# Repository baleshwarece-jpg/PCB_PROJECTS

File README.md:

# 30-Day PCB Design Challenge

A self-directed challenge to design, document, and release one original PCB per day for 30 consecutive days using KiCad 8. Each board lives in its own folder with complete hardware source files, gerbers, a bill of materials, and a standalone README covering the design rationale, schematic walkthrough, layout decisions, and common troubleshooting for that specific circuit.

The boards span power conversion, motor and LED driving, sensor interfacing, audio, wireless communication, and digital logic — chosen to force repeated practice across the categories of circuits that come up most often in embedded and electronics projects, rather than 30 variations on a single theme.

## Goals

- Build daily fluency with KiCad 8: schematic capture, footprint selection, layout, and gerber generation, fast enough to take a board from concept to fabrication-ready in a single day
- Practice real engineering judgment on every board — component selection backed by datasheet parameters, trace widths backed by IPC-2221, decoupling and grounding decisions backed by the actual current and noise behavior of the circuit, not copied defaults
- Produce documentation good enough that another engineer could understand, build, and troubleshoot each board without needing to ask questions
- Cover a broad enough range of circuit types that the challenge functions as a personal reference library going forward

## Repository Structure

Each day's board lives in its own top-level folder:

```
<repo-root>/
├── Day-01-AC-DC-Regulator/
├── Day-02-Transformerless-Power-Supply/
├── Day3_ServoTester/
├── Day4_MotorSpeedController/
├── DAY-5-LM389/
├── Day6-usb-5v-power-supply/
├── Day7-3.3v-LDO/
├── DAY8-ARDUINO-EXTENSIONBOARD/
├── Day9_pushbutton-led-controller/
├── Day10-DHT11/
├── Day11-I2C-OLED-ADAPTER/
├── Day12-IR-remote-receiver/
├── Day13_PIEZO-BUZZER/
├── DAY-14_LDRMODULE/
├── DAY15-RELAYMODULE/
├── DAY16-4LEV_BATTERY_INDICATOR/
├── DAY17-MCP23017-I2C-GPIO-Expander-Board/
├── DAY18_USB-UART-CONVERTER/
├── DAY19-WS2812B_RGB_LED_CONTROL/
├── DAY20-MOSFET_H_BRIDGE-MOTOR-DRIVER/
├── DAY21-Low-Power-Microphone-Preamplifier/
├── Day22-MCP2551-CAN-Bus-Transceiver-Breakout/
├── DAY23-SOIL_MOISTURE_SENSOR/
├── DAY24-NRF24-MODULE/
├── DAY25-LM2596-Adjustable-Buck-Converter/
├── DAY26-MAX7219-8-Digit-LED-Display-Driver/
├── DAY27-TPS61023-3.7V-LiPo-to-5V/
├── DAY28-74HC138-3-to-8/
├── DAY29-MPU6050/
└── DAY30-PAM8403-Class-D-Stereo-Amplifier/
```

Every folder follows the same internal layout:

```
DayNN-BoardName/
├── hardware/
│   ├── *.kicad_pro / *.kicad_sch / *.kicad_pcb
│   ├── gerbers/
│   └── bom/
├── docs/
│   ├── schematic.pdf
│   ├── datasheet(s)
│   └── assembly_notes.md
└── README.md
```

## Board Index

| Day | Board | Category |
|---|---|---|
| 01 | AC-DC Regulator | Power |
| 02 | Transformerless Power Supply | Power |
| 03 | Servo Tester | Motor / Actuator |
| 04 | Motor Speed Controller | Motor / Actuator |
| 05 | LM389 Audio Amplifier | Audio |
| 06 | USB to 5V Power Supply | Power |
| 07 | 3.3V LDO Regulator | Power |
| 08 | Arduino Extension Board | Prototyping |
| 09 | Pushbutton LED Controller | Digital I/O |
| 10 | DHT11 Temperature/Humidity Sensor Breakout | Sensor |
| 11 | I2C OLED Adapter | Display |
| 12 | IR Remote Receiver | Sensor / Comms |
| 13 | Piezo Buzzer Driver | Audio / Digital I/O |
| 14 | LDR Module | Sensor |
| 15 | Relay Module | Power / Switching |
| 16 | 4-Level Battery Indicator | Power / Sensor |
| 17 | MCP23017 I2C GPIO Expander | Digital Logic |
| 18 | USB to UART Converter | Comms |
| 19 | WS2812B RGB LED Strip Driver | LED / Motor-Adjacent |
| 20 | MOSFET H-Bridge Motor Driver | Motor / Actuator |
| 21 | Low-Power Microphone Preamplifier | Audio |
| 22 | MCP2551 CAN Bus Transceiver Breakout | Comms |
| 23 | Resistive Soil Moisture Sensor | Sensor |
| 24 | nRF24L01+ Wireless Module Adapter | Wireless |
| 25 | LM2596 Adjustable Buck Converter | Power |
| 26 | MAX7219 8-Digit LED Display Driver | Display |
| 27 | TPS61023 3.7V LiPo to 5V Boost Converter | Power |
| 28 | 74HC138 3-to-8 Line Decoder Breakout | Digital Logic |
| 29 | MPU6050 IMU Breakout | Sensor |
| 30 | PAM8403 Class-D Stereo Amplifier | Audio |

## Tooling

- **EDA:** KiCad 8
- **Fabrication target:** JLCPCB / PCBWay standard capabilities (2-layer, 1 oz / 2 oz copper depending on board, 0.6 mm minimum trace/space unless otherwise noted in a given board's README)
- **Reference standards:** IPC-2221 for trace current capacity; manufacturer datasheets for every active component's electrical and thermal limits

## Documentation Conventions

Every board's README follows a consistent structure: an overview of what the circuit does and why it's built the way it is, a full specifications table, a "why this design" section explaining the engineering reasoning behind component and layout choices (not just what the choices were), a per-component schematic walkthrough, PCB layout notes, getting-started wiring and code examples where applicable, a complete BOM with real part numbers, and a troubleshooting section covering realistic failure modes rather than generic advice.

## License

All hardware design files across this repository are released under **CERN OHL v2 — Permissive**, unless a specific board's folder states otherwise.

## Status

Challenge complete — 30 boards designed across 30 days, all folders accounted for. Individual board READMEs contain full design detail; this top-level README serves as the index.

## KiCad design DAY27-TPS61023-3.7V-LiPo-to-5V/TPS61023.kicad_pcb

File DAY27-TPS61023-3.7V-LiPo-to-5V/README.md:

# TPS61023 3.7V LiPo to 5V Boost Converter

**Day 27 / 30 — 30-Day PCB Design Challenge**

A single-cell LiPo to 5V step-up (boost) converter built around the TPS61023, a synchronous boost regulator with integrated power FETs, true load disconnect, and a 2.4 A switch current limit — purpose-built for portable projects that need a stable 5V rail from a single-cell lithium battery as it discharges from 4.2V down to 3.0V.

## Overview

A single-cell LiPo battery's terminal voltage spans roughly 3.0V (discharged cutoff) to 4.2V (full charge), straddling the 5V rail most peripherals and microcontroller boards expect. A linear regulator cannot produce 5V from a 3.7V-nominal source at all, since a linear regulator can only step voltage down. A boost converter is required, and the TPS61023 is a synchronous design — meaning the low-side switch is an actively driven FET rather than a passive diode, which removes the diode forward-voltage loss present in older asynchronous boost ICs and improves efficiency, particularly at low input voltages near end-of-discharge.

The TPS61023 also includes true shutdown (load disconnected from input during shutdown, unlike many boost ICs where the body diode of the synchronous FET still passes current to the load even when disabled) and a power-good output, both of which matter for battery-powered designs where parasitic leakage paths directly reduce runtime.

## Specifications

| Parameter | Value |
|---|---|
| Input Voltage | 0.5V – 5.5V (start-up requires ≥1.8V typical) |
| Output Voltage | 5.0V fixed (this board) — adjustable variants exist |
| Max Switch Current | 2.4A (internal current limit) |
| Max Output Current | ~1.2A at VIN = 3.0V, higher at higher VIN (load-line dependent) |
| Switching Frequency | 2.5 MHz typical |
| Quiescent Current | ~38 µA (device in regulation, no load) |
| True Shutdown | Yes — output disconnected from input via EN pin |
| Power Good Output | Open-drain, active high when VOUT within regulation |
| Package | SOT-23-Thin or WSON, this board uses SOT-23-Thin (6-pin) |
| PCB | 2-layer, 1 oz copper |

## Why a Dedicated Boost Board

A bare TPS61023 wired ad hoc on a breadboard will technically boost voltage, but several details determine whether it delivers rated current cleanly and survives a battery-powered duty cycle:

**Input capacitor placement and value:** At 2.5 MHz switching frequency, the inductor current ripple reflected onto the input rail needs low-ESR, low-ESL capacitance placed immediately at the VIN pin — a capacitor even 1 cm away on a long breadboard wire reintroduces enough parasitic inductance to produce audible noise (coil whine) and degraded efficiency. This board places the input ceramic capacitor directly adjacent to the VIN pin with minimal trace length.

**Output capacitor ESR and the feedback loop:** Boost converters are inherently right-half-plane-zero systems, meaning loop stability is more sensitive to output capacitor ESR than in a comparable buck design. The TPS61023's internal compensation is designed around the datasheet's recommended output capacitor range — substituting a much larger or much smaller value, or a high-ESR electrolytic, can degrade transient response or introduce ringing on load steps.

**Inductor saturation margin:** The boost topology's inductor carries higher peak current than the output current would suggest, since input current exceeds output current by roughly the inverse of efficiency times the voltage step-up ratio. At VIN = 3.0V boosting to 5V and drawing 1A out, input-side (and inductor) current approaches 1.85A even at 90% efficiency. An inductor saturation-rated only slightly above the IC's switch current limit will saturate under real load before the IC's own current limit engages, producing unpredictable output collapse rather than a clean current-limited response.

**True shutdown current path:** EN tied low disconnects the load from the battery entirely on this device, which only matters if the EN pin is actually routed to an accessible control point — many ad hoc breadboard builds simply tie EN high permanently, losing the ability to fully disconnect the battery for storage or fault conditions.

## Schematic Overview

**U1 — TPS61023**
Synchronous boost converter. VIN connects to the LiPo input. SW connects to the inductor switch node. VOUT is the regulated 5V output. EN is broken out to a control header with a pull-up to VIN for default-on behavior. PG (power good) is broken out as an open-drain output with an external pull-up.

**L1 — 1.5 µH Power Inductor**
Selected per the TPS61023 datasheet's recommended inductance range for 2.5 MHz switching. Saturation current rated at 4A — comfortably above the IC's 2.4A switch current limit to ensure the IC's current limit, not inductor saturation, defines the converter's overcurrent behavior.

**C1 — 10 µF Ceramic, X7R (Input)**
Input decoupling, placed directly at the VIN pin. X7R dielectric specified rather than X5R or lower grades to limit capacitance derating under DC bias and temperature, since ceramic capacitors lose significant effective capacitance as DC bias approaches their rated voltage.

**C2 — 22 µF Ceramic, X7R (Output)**
Output filter capacitor, within the TPS61023 datasheet's recommended range for stable loop compensation. Two parallel 22 µF capacitors are used on the footprint pads to split ripple current and reduce effective ESR further, though a single capacitor is sufficient for most loads.

**R1 — 100 kΩ Pull-up (EN)**
Pulls EN to VIN by default so the converter starts automatically when the battery is connected. EN header pin allows pulling this low externally (through a switch or MCU GPIO) to fully disconnect the load.

**R2 — 100 kΩ Pull-up (PG)**
Pull-up for the open-drain power-good output, referenced to VOUT so the PG signal swings to a valid logic high recognizable by a downstream 5V-logic MCU.

**J1 — Battery input**
2-pin JST-PH 2.0mm connector, standard polarity for common LiPo battery connectors.

**J2 — Output / control header**
4-pin, 2.54 mm: VOUT, GND, EN, PG.

**LED1 — Power-good indicator**
Green, 0603, driven from the PG pull-up node rather than directly from VOUT, so the LED only illuminates once the converter has actually reached regulation rather than simply being powered.

## PCB Design Notes

- Designed in KiCad 8
- 1 oz copper, 2-layer — sufficient for the ~1–2A current levels involved given short, wide power traces
- Switch node (U1 SW → L1) kept short and on a single layer to minimize parasitic inductance and EMI radiation at 2.5 MHz
- Input capacitor (C1) placed on the same side as U1 with trace length to VIN under 3 mm
- Output capacitor (C2) placed adjacent to VOUT, ground return tied directly into the ground pour beneath the IC
- Ground pour on both layers, stitched with vias around the IC and inductor footprint
- Feedback/PG/EN traces routed away from the switch node to avoid noise injection into control signals
- Battery connector polarity clearly marked on silkscreen, reverse-polarity protection diode footprint provided as an optional series component on VIN (not populated by default, since the TPS61023 itself has no reverse-input protection)
- Mounting holes: 2× M2.5, diagonal corners

## Getting Started

### Wiring

```
LiPo Battery (3.7V nominal)     Boost Board           Load (5V)
─────────────────────────────────────────────────────────────────
JST-PH connector  ──────>       J1 (VIN/GND)
                                  VOUT       ──────>    + Load
                                  GND        ──────>    − Load
                                  EN         ──────>    (tied high by default)
                                  PG         ──────>    optional MCU input
```

A LiPo protection circuit (over-discharge, over-current) is assumed to be present either in the battery pack itself or upstream of this board — the TPS61023 provides no battery protection functions on its own.

### Checking Power-Good Status (Arduino example)

```cpp
const int PG_PIN = 2;

void setup() {
  pinMode(PG_PIN, INPUT);
  Serial.begin(9600);
}

void loop() {
  bool regulating = digitalRead(PG_PIN);
  Serial.println(regulating ? "5V rail OK" : "5V rail not in regulation");
  delay(500);
}
```

## BOM

| Reference | Part | Package | Value / Part No. |
|---|---|---|---|
| U1 | TPS61023 | SOT-23-Thin (6-pin) | Synchronous boost converter |
| L1 | Shielded power inductor | 3×3 mm | 1.5 µH, Isat > 4A |
| C1 | Ceramic, X7R | 0805 | 10 µF / 10V |
| C2 | Ceramic, X7R | 0805 | 22 µF / 10V |
| R1 | Resistor | 0402 | 100 kΩ (EN pull-up) |
| R2 | Resistor | 0402 | 100 kΩ (PG pull-up) |
| R3 | Resistor | 0402 | 1 kΩ (LED current limit) |
| LED1 | Green LED | 0603 | Power-good indicator |
| J1 | JST-PH connector | 2.0 mm, 2-pin | Battery input |
| J2 | Pin header | 2.54 mm, 4-pin | Output / control |

## Common Issues

**Output sags or shuts down under load near end-of-discharge**
Expected behavior as the battery approaches its discharge cutoff — the IC needs sufficient input voltage headroom to maintain the duty cycle required for 5V output, and as VIN drops the maximum deliverable output current also drops. Check the actual battery voltage under load with a meter before assuming a board fault.

**Audible whine from the inductor**
Usually indicates either light-load operation triggering pulse-skipping mode (some buzz is normal and not damaging) or insufficient input capacitance allowing ripple current through the inductor at audible sub-harmonics. Confirm C1 is populated and properly soldered before assuming the inductor itself is at fault.

**PG pin never goes high**
Confirm R2 is populated — PG is open-drain and will float or read indeterminate without an external pull-up. Also verify VOUT is actually reaching 5V; PG asserts only once the output is within the IC's regulation window.

**No output despite input voltage present**
Check EN is pulled high — if R1 is missing or EN is inadvertently grounded through the control header, the converter remains in shutdown regardless of VIN.

**Converter does not start from a fully discharged battery**
The TPS61023 requires a minimum input voltage (datasheet typical ~1.8V) to begin switching. A battery below its rated discharge cutoff (commonly 3.0V) should not be relied upon to start the converter — this is a battery protection concern as much as a converter one.

## Repository Structure

```
TPS61023-Boost-Converter/
├── hardware/
│   ├── TPS61023_Boost.kicad_pro
│   ├── TPS61023_Boost.kicad_sch
│   ├── TPS61023_Boost.kicad_pcb
│   ├── gerbers/
│   │   └── TPS61023_Boost_gerbers.zip
│   └── bom/
│       └── TPS61023_Boost_BOM.csv
├── docs/
│   ├── schematic.pdf
│   ├── TPS61023_Datasheet.pdf
│   └── assembly_notes.md
└── README.md
```

## 30-Day PCB Challenge Progress

| Day | Board | Status |
|---|---|---|
| 25 | LM2596 Adjustable Buck Converter | Complete |
| 26 | MAX7219 8-Digit LED Display Driver | Complete |
| 27 | TPS61023 3.7V LiPo to 5V Boost Converter | Complete |
| 28 | Coming soon | — |

## License

Hardware design files released under CERN OHL v2 — Permissive.

## References

- TPS61023 Datasheet — Texas Instruments
- KiCad EDA

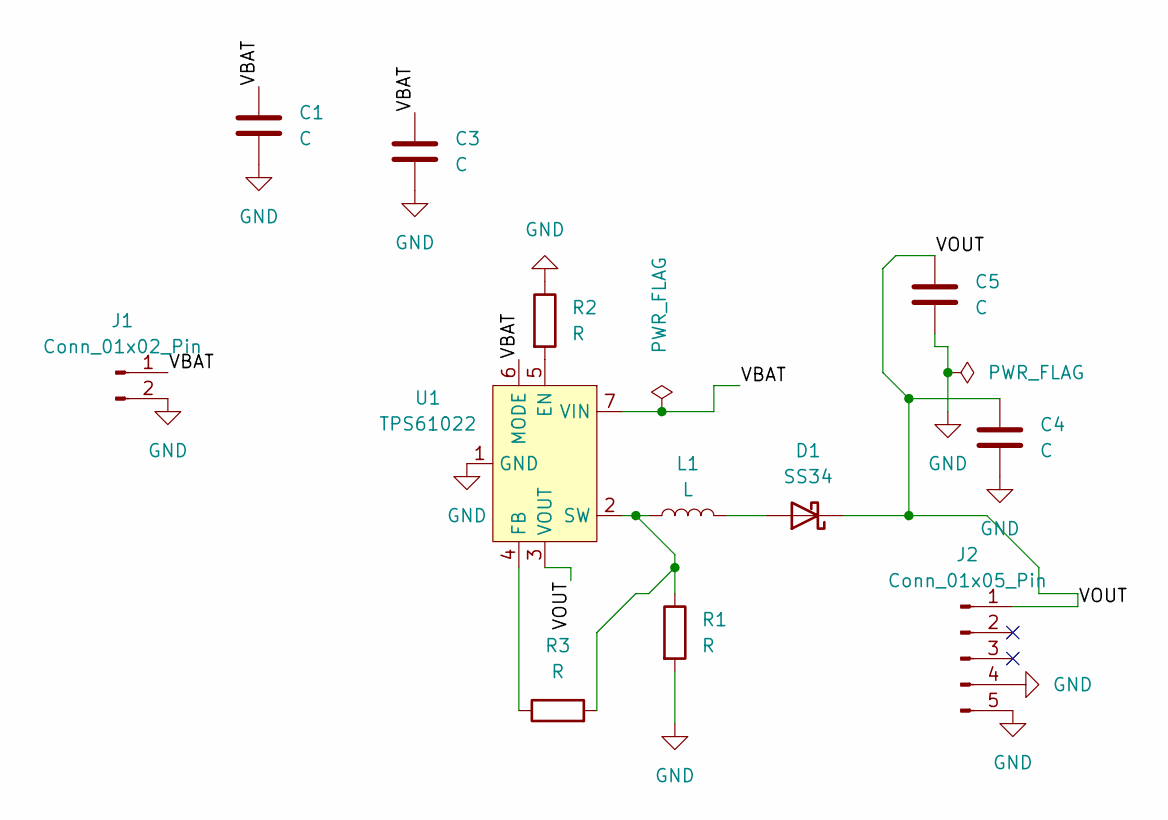
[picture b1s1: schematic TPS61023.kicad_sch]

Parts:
C1, C3, C4, C5: C; C_0603_1608Metric_Pad1.08x0.95mm_HandSolder
D1: SS34; D_SMA
J1: Conn_01x02_Pin; PinHeader_1x02_P2.54mm_Vertical
J2: Conn_01x05_Pin; PinHeader_1x05_P2.54mm_Horizontal
L1: L; L_0603_1608Metric_Pad1.05x0.95mm_HandSolder
R1, R2, R3: R; R_0603_1608Metric_Pad0.98x0.95mm_HandSolder
U1: TPS61022; Texas_RWU0007A_VQFN-7_2x2mm_P0.5mm

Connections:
/VBAT: C1.1, C3.1, J1.1, U1.6 (MODE), U1.7 (VIN); also elsewhere on the board
/VOUT: C4.1, C5.1, D1.1 (K), J2.1, U1.3 (VOUT)
GND: C1.2, C3.2, C4.2, C5.2, J1.2, J2.4, J2.5, R1.2, R2.1, U1.1 (GND); also elsewhere on the board
unnamed: D1.2 (A), L1.2
unnamed: R2.2, U1.5 (EN)
unnamed: R3.1, U1.4 (FB)
unnamed: L1.1, R1.1, R3.2, U1.2 (SW)

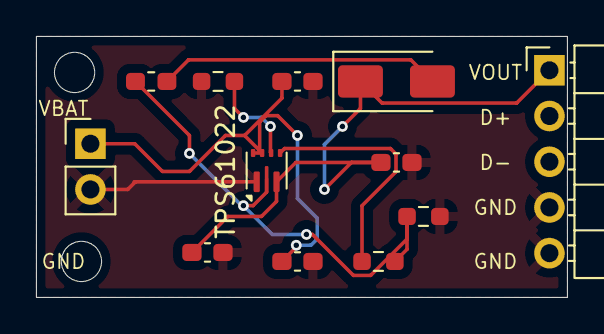
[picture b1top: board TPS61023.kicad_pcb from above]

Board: 2 copper layers, 29.5 x 14.5 mm, 12 parts (0 on the bottom side), 7 nets.

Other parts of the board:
VBAT: Conn_01x02_Pin; PinHeader_1x02_P2.54mm_Vertical

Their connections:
/VBAT: VBAT.1; also elsewhere on the board
GND: VBAT.2; also elsewhere on the board

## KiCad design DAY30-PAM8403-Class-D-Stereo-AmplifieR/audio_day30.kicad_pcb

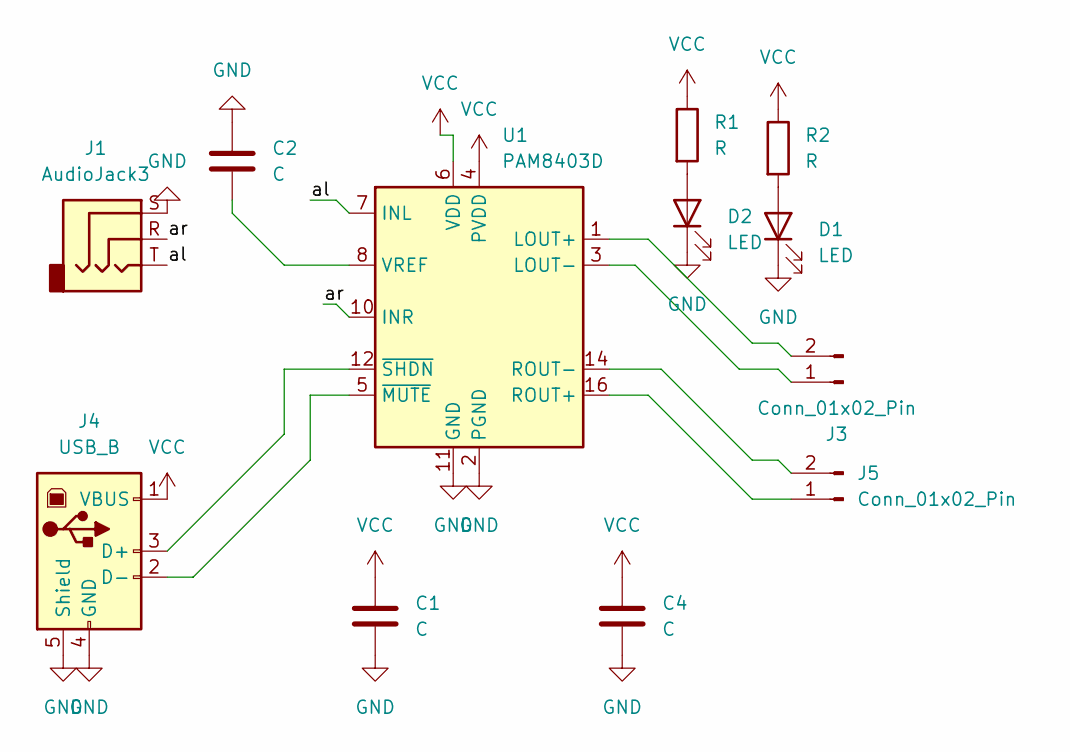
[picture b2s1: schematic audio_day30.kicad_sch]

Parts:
C1, C2, C4: C; C_0603_1608Metric_Pad1.08x0.95mm_HandSolder
D1, D2: LED; LED_0603_1608Metric_Pad1.05x0.95mm_HandSolder
J1: AudioJack3; Jack_3.5mm_CUI_SJ1-3523N_Horizontal
J3, J5: Conn_01x02_Pin; PinHeader_1x02_P2.54mm_Vertical
J4: USB_B; USB_Mini-B_Lumberg_2486_01_Horizontal
R1, R2: R; R_0805_2012Metric_Pad1.20x1.40mm_HandSolder
U1: PAM8403D; SOIC-16_3.9x9.9mm_P1.27mm

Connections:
/al: J1.T, U1.7 (INL)
/ar: J1.R, U1.10 (INR)
GND: C1.2, C2.1, C4.2, D1.1 (K), D2.1 (K), J1.S, J4.4 (GND), J4.5 (Shield), U1.2 (PGND), U1.11 (GND), U1.15 (PGND)
unnamed: D1.2 (A), R2.2
unnamed: D2.2 (A), R1.2
unnamed: J3.1, U1.3 (LOUT-)
unnamed: J3.2, U1.1 (LOUT+)
unnamed: J4.3 (D+), U1.12 (~SHDN)
unnamed: J4.2 (D-), U1.5 (~MUTE)
unnamed: J5.1, U1.16 (ROUT+)
unnamed: J5.2, U1.14 (ROUT-)
unnamed: C2.2, U1.8 (VREF)
VCC: C1.1, C4.1, J4.1 (VBUS), R1.1, R2.1, U1.4 (PVDD), U1.6 (VDD), U1.13 (PVDD)

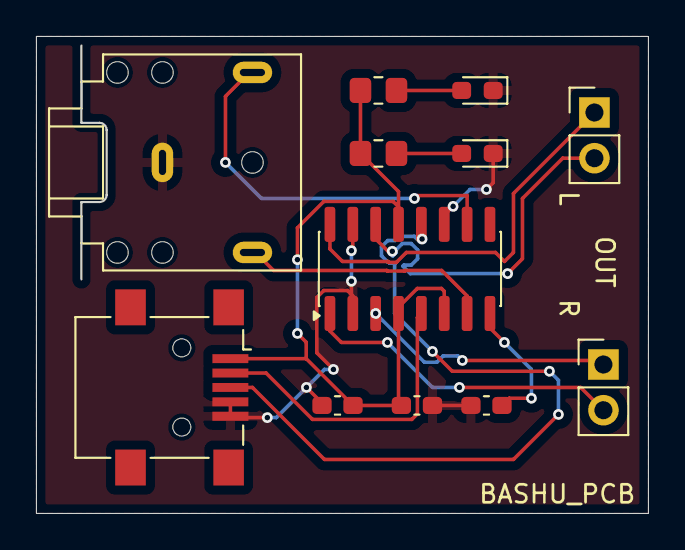
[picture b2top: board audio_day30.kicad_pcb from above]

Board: 2 copper layers, 34.0 x 26.5 mm, 12 parts (0 on the bottom side), 13 nets.

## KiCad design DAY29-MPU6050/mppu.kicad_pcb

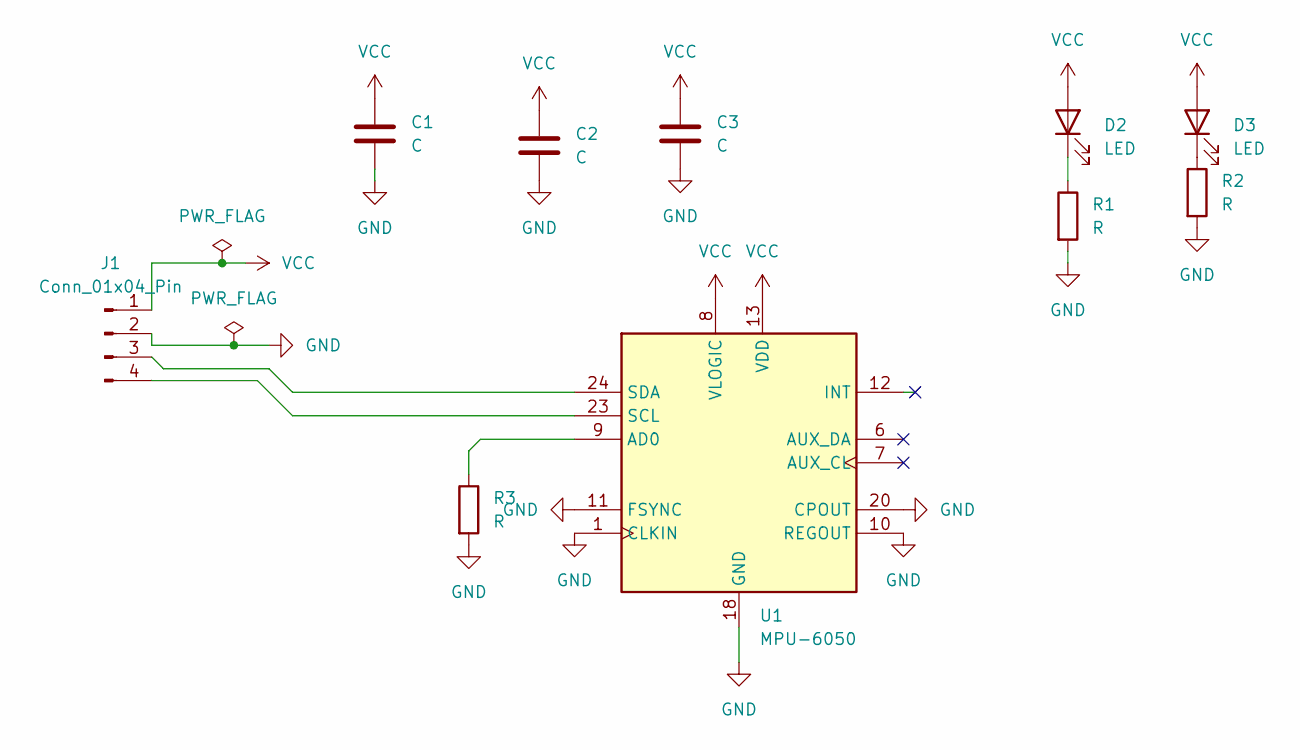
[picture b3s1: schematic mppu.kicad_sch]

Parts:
C1, C2, C3: C; C_0805_2012Metric_Pad1.18x1.45mm_HandSolder
D2, D3: LED; LED_0603_1608Metric_Pad1.05x0.95mm_HandSolder
J1: Conn_01x04_Pin; PinHeader_1x04_P2.54mm_Vertical
R1, R2, R3: R; R_0805_2012Metric_Pad1.20x1.40mm_HandSolder
U1: MPU-6050; InvenSense_QFN-24_4x4mm_P0.5mm

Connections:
GND: C1.2, C2.2, C3.2, J1.2, R1.2, R2.2, R3.2, U1.1 (CLKIN), U1.10 (REGOUT), U1.11 (FSYNC), U1.18 (GND), U1.20 (CPOUT)
unnamed: D2.1 (K), R1.1
unnamed: D3.1 (K), R2.1
unnamed: J1.3, U1.24 (SDA)
unnamed: J1.4, U1.23 (SCL)
unnamed: R3.1, U1.9 (AD0)
VCC: C1.1, C2.1, C3.1, D2.2 (A), D3.2 (A), J1.1, U1.8 (VLOGIC), U1.13 (VDD)

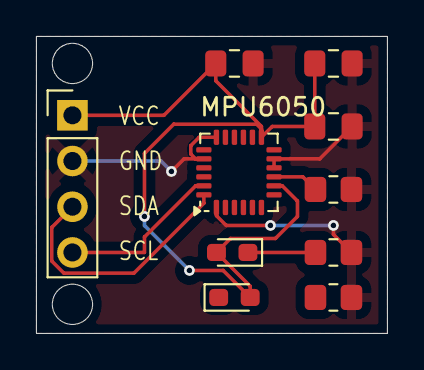
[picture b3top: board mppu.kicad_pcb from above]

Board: 2 copper layers, 19.5 x 16.5 mm, 10 parts (0 on the bottom side), 7 nets.

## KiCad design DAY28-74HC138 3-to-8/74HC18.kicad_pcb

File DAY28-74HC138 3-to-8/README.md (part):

# 74HC138 3-to-8 Line Decoder Breakout Board

**Day 28 / 30 — 30-Day PCB Design Challenge**

A breakout board for the 74HC138, a 3-to-8 line decoder/demultiplexer commonly used to extend a microcontroller's limited GPIO count into multiple chip-select lines for SPI peripherals, address decoding in memory-mapped designs, or driving up to 8 mutually-exclusive outputs from a 3-bit binary code.

## Overview

Many projects reach a point where a microcontroller runs out of dedicated chip-select or enable lines before it runs out of other I/O — a common case being multiple SPI devices on a shared bus, each needing its own CS line. Wiring 8 separate GPIOs as individual chip-selects works but consumes pins quickly and scales poorly. The 74HC138 takes a 3-bit binary address (A0–A2) plus three enable inputs and asserts exactly one of 8 active-low outputs at a time, meaning 3 GPIO pins can select among 8 devices instead of needing 8 dedicated lines.

This is a standard combinational logic part with no internal state or configuration registers — outputs change immediately and combinationally based on the address and enable inputs, with no clock or serial protocol involved. This board exists primarily to provide clean decoupling, a accessible header layout, and a documented reference for a part that gets reused across many other projects in this challenge series.

## Specifications

| Parameter | Value |
|---|---|
| Supply Voltage | 2V – 6V (4.5V–5.5V typical for this board) |
| Logic Family | 74HC (CMOS), 5V-tolerant inputs at VCC = 5V |
| Propagation Delay | ~18 ns typical (VCC = 5V, address to output) |
| Output Type | Active-low, push-pull (not open-drain) |
| Output Current | ±6 mA per output (HC family standard) |
| Address Inputs | A0, A1, A2 (3-bit binary select) |
| Enable Inputs | E1 (active-low), E2 (active-low), E3 (active-high) |
| Outputs | Y0–Y7, active-low, one asserted at a time |
| Package | SOIC-16 |
| PCB | 2-layer, 1 oz copper |

## Why a Breakout Board for a Simple Logic IC

The 74HC138 has no failure modes exotic enough to justify much circuit complexity, but a few practical details make a dedicated board worth having on hand rather than dead-bugging the IC into a project each time:

**Unused enable pins left floating:** The 74HC138 has three enable inputs (E1, E2 active-low; E3 active-high) — all three must be in their active state for any output to assert. A breadboard wiring mistake that leaves one enable pin floating produces unpredictable output behavior, since CMOS inputs left floating can settle at intermediate voltages and draw excess supply current or oscillate. This board ties E2 and E3 to their active states by default via solder-jumper pads, leaving only E1 broken out to a header pin for the common use case of a single active-low chip-enable signal from the host MCU.

**Decoupling for clean address transitions:** Like any CMOS logic device, the 74HC138 draws a brief current spike each time multiple outputs switch simultaneously during an address change (one output deasserting while another asserts). Without local decoupling this can show up as a glitch on the shared supply rail, which on a board with other sensitive analog or RF circuitry sharing the same rail is worth avoiding even though the HC138 itself is a low-power part.

**Output glitching during address transitions:** Because this is a combinational (not latched) decoder, outputs can briefly glitch through unintended states during an address transition if the three address bits do not change perfectly simultaneously — a phenomenon inherent to ripple-through binary decoding, not a fault of this board. Devices sensitive to brief false chip-select pulses (some SPI flash parts, for example) may need the enable pin gated by the host MCU only after address lines have settled, which is a software/timing consideration documented here rather than something correctable in hardware.

## Schematic Overview

**U1 — 74HC138**
3-to-8 decoder. A0–A2 address inputs from the header. E1 active-low enable from the header. E2 tied low via solder jumper (default enabled). E3 tied high via solder jumper (default enabled). Y0–Y7 outputs broken out to the output header.

**C1 — 100 nF Ceramic**
Local decoupling at VCC, placed within 2 mm of the IC supply pin per standard CMOS logic decoupling practice.

**JP1, JP2 — Solder jumpers (E2, E3 default state)**
Default-closed jumpers tying E2 low and E3 high so the device is enabled out of the box using only the E1 pin as an active-low chip enable. Can be cut and the pads broken out to header pins instead if all three enables need independent control for a specific application (e.g., using the decoder as a true 4-to-16 demultiplexer with a second 74HC138).

**J1 — Input header**
5-pin, 2.54 mm: VCC, GND, A0, A1, A2.

**J2 — Enable header**
2-pin, 2.54 mm: E1, GND (reference for an external pull-down switch or direct MCU GPIO connection).

**J3 — Output header**
8-pin, 2.54 mm: Y0–Y7, silkscreen-labeled in binary order matching the truth table for unambiguous wiring.

**LED1 — Power indicator**
Green, 0603, 1 kΩ series resistor from VCC, independent of the decoder outputs.

## Truth Table Reference

| E1 | E2 | E3 | A2 A1 A0 | Active Output |
|---|---|---|---|---|
| H | X | X | XXX | None (all outputs HIGH) |
| X | H | X | XXX | None (all outputs HIGH) |
| X | X | L | XXX | None (all outputs HIGH) |
| L | L | H | 000 | Y0 LOW |
| L | L | H | 001 | Y1 LOW |
| L | L | H | 010 | Y2 LOW |
| L | L | H | 011 | Y3 LOW |
| L | L | H | 100 | Y4 LOW |
| L | L | H | 101 | Y5 LOW |
| L | L | H | 110 | Y6 LOW |
| L | L | H | 111 | Y7 LOW |

## PCB Design Notes

- Designed in KiCad 8
- 1 oz copper, 2-layer — currents involved are well under 10 mA per line, so the layout priority is clean labeling and connector accessibility rather than current capacity
- C1 placed directly adjacent to VCC pin with the shortest practical ground return to the ground pour
- Address input traces (A0–A2) kept equal length where practical to minimize skew-induced output glitching during fast address transitions
- Output header silkscreen labeled Y0–Y7 directly above each pin, with the corresponding 3-bit binary address also silkscreened beneath each label for quick reference without consulting the datasheet
- Ground pour on both layers, stitched with vias around the IC footprint
- Mounting holes: 2× M2.5, diagonal corners

## Getting Started

### Wiring (single chip-enable use case)

```
Host MCU                   Decoder Board          Selected Devices
──────────────────────────────────────────────────────────────────
5V              ──────>    VCC
GND             ──────>    GND
GPIO (A0)       ──────>    A0
GPIO (A1)       ──────>    A1
GPIO (A2)       ──────>    A2
GPIO (E1, active-low) ──>  E1
                            Y0–Y7      ──────>    Individual CS pins
```

E2 and E3 remain tied to their active states via the default-closed solder jumpers; only E1 needs to be driven, low to enable decoding and high to force all outputs inactive.

### Arduino Example (selecting one of 8 SPI devices)

```cpp
const int A0_PIN = 2;
const int A1_PIN = 3;
const int A2_PIN = 4;
const int E1_PIN = 5;

void setup() {
  pinMode(A0_PIN, OUTPUT);
  pinMode(A1_PIN, OUTPUT);
  pinMode(A2_PIN, OUTPUT);
  pinMode(E1_PIN, OUTPUT);
  digitalWrite(E1_PIN, HIGH); // start disabled
}

void selectDevice(uint8_t index) {
  digitalWrite(E1_PIN, HIGH);          // disable while address settles
  digitalWrite(A0_PIN, index & 0x01);
  digitalWrite(A1_PIN, (index >> 1) & 0x01);
  digitalWrite(A2_PIN, (index >> 2) & 0x01);
  digitalWrite(E1_PIN, LOW);           // enable once address is stable
}

void loop() {
  selectDevice(3); // asserts Y3
  // ... perform SPI transaction with device 3 ...
  digitalWrite(E1_PIN, HIGH); // deselect before changing address again
  delay(100);
}
```

## BOM

| Reference | Part | Package | Value / Part No. |
|---|---|---|---|
| U1 | 74HC138 | SOIC-16 | 3-to-8 line decoder |
| C1 | Ceramic | 0603 | 100 nF / 16V |
| R1 | Resistor | 0402 | 1 kΩ (LED current limit) |
| LED1 | Green LED | 0603 | Power indicator |
| JP1, JP2 | Solder jumper pads | — | E2/E3 default-state straps |
| J1 | Pin header | 2.54 mm, 5-pin | VCC, GND, A0–A2 |
| J2 | Pin header | 2.54 mm, 2-pin | E1, GND |
| J3 | Pin header | 2.54 mm, 8-pin | Y0–Y7 outputs |

## Common Issues

**No output ever asserts, all outputs stay high**
Check that both solder jumpers JP1 (E2) and JP2 (E3) are intact and that E1 is actually being driven low — all three enable conditions must be satisfied simultaneously, not just E1.

**Wrong output asserts for a given address**
Verify A0 is the least significant bit, not A2 — this is a common wiring swap. Cross-reference against the truth table silkscreened beneath the output header.

**Brief glitches on unintended outputs during address changes**
Expected behavior of a combinational decoder if address bits do not transition simultaneously. If driving a device sensitive to brief false selection, gate the connected device's chip-select-sensitive operation through E1 as shown in the example code: disable via E1 before changing the address, then re-enable once the address lines have settled.

**Excess current draw or warm IC at idle**
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
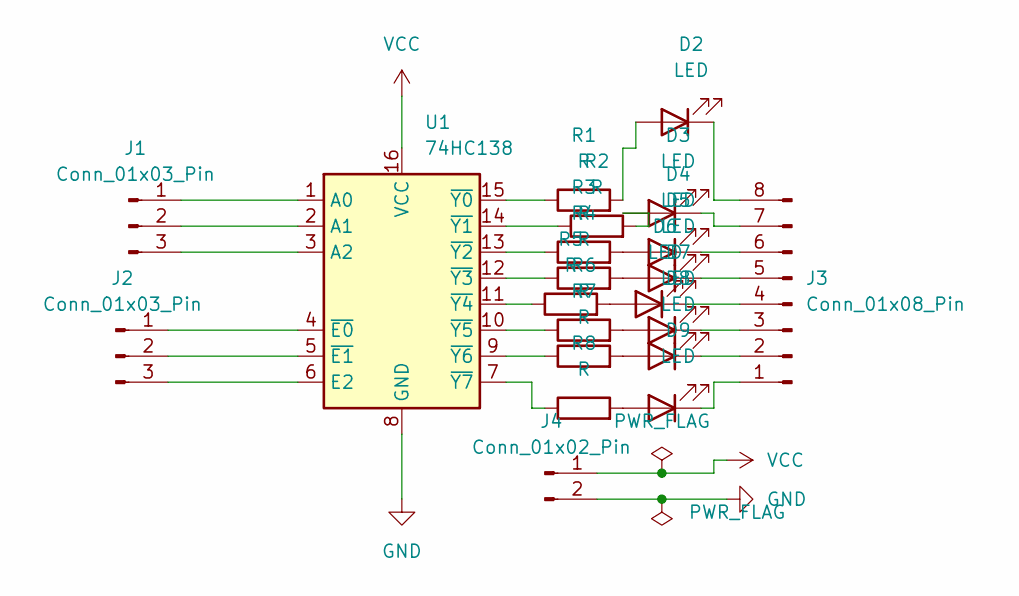
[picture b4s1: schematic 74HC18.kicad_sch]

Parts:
D2, D3, D4, D5, D6, D7, D8, D9: LED; LED_0805_2012Metric_Pad1.15x1.40mm_HandSolder
J1, J2: Conn_01x03_Pin; PinSocket_1x03_P2.54mm_Vertical
J3: Conn_01x08_Pin; PinSocket_1x08_P2.54mm_Vertical
J4: Conn_01x02_Pin; PinHeader_1x02_P2.54mm_Vertical
R1, R2, R3, R4, R5, R6, R7, R8: R; R_0805_2012Metric_Pad1.20x1.40mm_HandSolder
U1: 74HC138; DIP-16_W10.16mm_LongPads

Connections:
GND: J4.2, U1.8 (GND)
unnamed: D2.2 (A), R1.2
unnamed 2: D2.1 (K), J3.8; also elsewhere on the board
unnamed: D3.2 (A), R2.2
unnamed 4: D3.1 (K), J3.7; also elsewhere on the board
unnamed: D4.2 (A), R3.2
unnamed 6: D4.1 (K), J3.6; also elsewhere on the board
unnamed: D5.2 (A), R4.2
unnamed 8: D5.1 (K), J3.5; also elsewhere on the board
unnamed: D6.2 (A), R5.2
unnamed 10: D6.1 (K), J3.4; also elsewhere on the board
unnamed: D7.2 (A), R6.2
unnamed 12: D7.1 (K), J3.3; also elsewhere on the board
unnamed: D8.2 (A), R7.2
unnamed 14: D8.1 (K), J3.2; also elsewhere on the board
unnamed: D9.2 (A), R8.2
unnamed 16: D9.1 (K), J3.1; also elsewhere on the board
unnamed: J1.1, U1.1 (A0)
unnamed: J1.2, U1.2 (A1)
unnamed: J1.3, U1.3 (A2)
unnamed: J2.1, U1.4 (~E0)
unnamed: J2.2, U1.5 (~E1)
unnamed: J2.3, U1.6 (E2)
unnamed: R1.1, U1.15 (~Y0)
unnamed: R2.1, U1.14 (~Y1)
unnamed: R3.1, U1.13 (~Y2)
unnamed: R4.1, U1.12 (~Y3)
unnamed: R5.1, U1.11 (~Y4)
unnamed: R6.1, U1.10 (~Y5)
unnamed: R7.1, U1.9 (~Y6)
unnamed: R8.1, U1.7 (~Y7)
VCC: J4.1, U1.16 (VCC)

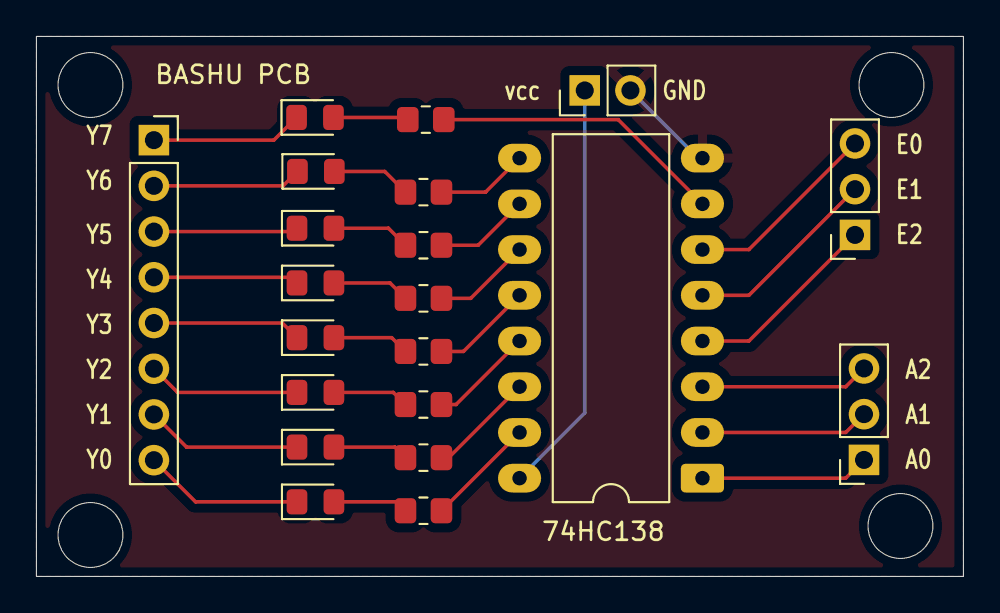
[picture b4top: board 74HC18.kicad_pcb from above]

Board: 2 copper layers, 51.5 x 30.0 mm, 21 parts (0 on the bottom side), 32 nets.

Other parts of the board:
Y7: Conn_01x08_Pin; PinSocket_1x08_P2.54mm_Vertical

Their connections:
unnamed 2: Y7.8; also elsewhere on the board
unnamed 4: Y7.7; also elsewhere on the board
unnamed 6: Y7.6; also elsewhere on the board
unnamed 8: Y7.5; also elsewhere on the board
unnamed 10: Y7.4; also elsewhere on the board
unnamed 12: Y7.3; also elsewhere on the board
unnamed 14: Y7.2; also elsewhere on the board
unnamed 16: Y7.1; also elsewhere on the board

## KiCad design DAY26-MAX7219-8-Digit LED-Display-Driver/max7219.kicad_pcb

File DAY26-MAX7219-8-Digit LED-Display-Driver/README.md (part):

# MAX7219 8-Digit LED Display Driver

**Day 26 / 30 — 30-Day PCB Design Challenge**

A driver board built around the MAX7219, which multiplexes and current-limits up to 8 digits of 7-segment LED displays (or a 64-LED dot matrix) from a single SPI-like 3-wire interface, eliminating the need to drive 64+ individual GPIO pins or external current-limiting resistors per segment.

## Overview

Driving multiple 7-segment displays directly from a microcontroller requires either one GPIO per segment per digit (impractical past 1–2 digits) or a multiplexed scan routine where the MCU rapidly cycles through digits, sinking and sourcing current itself while managing timing to avoid visible flicker — all while still needing external current-limiting resistors on every segment line, since GPIOs have no built-in current regulation.

The MAX7219 solves this by integrating an 8x8 static RAM (one row per digit), a BCD or raw-segment decoder, multiplex scan circuitry, and a single external resistor that sets segment current for all digits simultaneously via an internal current-mirror reference. The host MCU only needs 3 pins (DIN, CLK, LOAD/CS) and writes digit data as 16-bit words over a simple shift-register-style protocol — no real-time refresh loop required, since the MAX7219 handles multiplexing internally and continues driving the display even while the MCU is busy with other tasks.

## Specifications

| Parameter | Value |
|---|---|
| Supply Voltage | 4.0V – 5.5V DC |
| Segment Current Range | 4 mA – 40 mA per segment (set by RSET) |
| Digit Drive | 8 digits, common-cathode, multiplexed |
| Interface | 3-wire (DIN, CLK, LOAD/CS), SPI-compatible, up to 10 MHz |
| Display Support | 7-segment numeric, bar graph, or 8x8 dot matrix (raw segment mode) |
| Daisy-Chainable | Yes — DOUT of one device feeds DIN of next |
| Brightness Control | 16 steps, software-controlled via intensity register |
| Package | DIP-24 or SOIC-24 |
| PCB | 2-layer, 1 oz copper |

## Why a Dedicated Driver Board

Wiring a MAX7219 directly on a breadboard with a generic display module works for a demo, but a few details determine whether the result is reliable in continuous use:

**Current-set resistor accuracy:** Segment current is set by a single resistor from V+ to the ISET pin, with the relationship approximately ISEG ≈ 100 / RSET (RSET in kΩ, ISEG in mA). A common error is using a low-tolerance resistor here, since this single resistor sets brightness uniformity across all 64 segments — a 5% resistor tolerance directly becomes a 5% brightness variance between otherwise identical boards. This board uses a 1% metal film resistor for RSET.

**Decoupling at the digit drivers:** Each multiplex cycle switches a digit's common cathode and up to 8 segment sources simultaneously, producing current transients an order of magnitude larger than a typical logic IC. Without adequate local decoupling, this shows up as visible flicker or brightness modulation correlated with which digit is active. A bulk capacitor and a local ceramic are placed directly at the IC's V+ pin.

**Daisy-chain signal integrity:** When multiple MAX7219s are chained (common in larger displays), DOUT-to-DIN trace length and the LOAD/CS line's simultaneous assertion across all chained devices both affect maximum reliable clock rate. This board breaks out DIN/CLK/LOAD and DOUT/CLK/LOAD on opposite edges specifically to support clean daisy-chaining without rerouting jumpers.

**ISET pin sensitivity:** The ISET pin is a high-impedance current-reference input — noise coupled onto this trace from adjacent digit-drive lines shows up as instability in displayed brightness. It is routed away from the digit and segment driver traces on this board.

## Schematic Overview

**U1 — MAX7219CNG**
LED display driver. DIN/CLK/LOAD on the input side. SEG A–G/DP and DIG0–DIG7 connect to the display header. ISET sets segment current via R1. V+ decoupled locally and with bulk capacitance.

**R1 — 10 kΩ, 1% (RSET)**
Sets segment current per ISEG ≈ 100/RSET (kΩ). At 10 kΩ this gives approximately 10 mA per segment — a reasonable default for typical common-cathode 7-segment displays without excessive total board current. Footprint allows substitution down to ~1 kΩ for higher brightness applications (display-dependent maximum).

**C1 — 10 µF Electrolytic**
Bulk decoupling at V+, supports the current transients from multiplexed digit switching.

**C2 — 100 nF Ceramic**
Local high-frequency decoupling, placed within 2 mm of the V+ pin per the MAX7219 datasheet's recommended decoupling practice.

**J1 — Input header**
6-pin, 2.54 mm: VCC, GND, DIN, CLK, LOAD/CS — plus a DOUT pin broken out adjacent for convenience when not daisy-chaining.

**J2 — Daisy-chain output header**
4-pin, 2.54 mm: DOUT, CLK, LOAD/CS, GND — positioned at the opposite edge of the board from J1 so that chained boards can be placed end-to-end with minimal jumper length.

**J3 — Display header**
12-pin, 2.54 mm, broken into two rows: SEG A–G/DP (8 pins) and DIG0–DIG7 (8 pins), laid out to match common off-the-shelf 7-segment display module pinouts where practical.

**LED1 — Power indicator**
Green, 0603, 1 kΩ series resistor from V+, independent of the display digit lines.

## PCB Design Notes

- Designed in KiCad 8
- 1 oz copper, 2-layer — digit/segment drive currents are low per-line (tens of mA), so layout priorities are noise isolation and trace routing density rather than current capacity
- ISET trace (R1 to U1 pin 18) routed with no parallel run alongside any SEG or DIG trace, kept short
- C1/C2 placed directly adjacent to V+ pin, ground return routed straight to the ground pour beneath the IC rather than around the board perimeter
- DIN/CLK/LOAD input group and DOUT/CLK/LOAD output group placed on opposite board edges to support clean daisy-chaining in multi-module displays
- Ground pour on both layers, stitched with vias around the IC perimeter
- Silkscreen labels each segment header pin (A–G, DP, DIG0–7) to avoid display-wiring mistakes during assembly
- Mounting holes: 4× M2.5, 3 mm from board edge at each corner

## Getting Started

### Wiring

```
Host MCU (SPI-capable)     Driver Board          7-Segment Display
──────────────────────────────────────────────────────────────────
5V              ──────>    VCC
GND             ──────>    GND
Digital Pin     ──────>    DIN
Digital Pin     ──────>    CLK
Digital Pin     ──────>    LOAD/CS
                            SEG A–G/DP  ──────>   Segment pins
                            DIG0–DIG7   ──────>   Digit common pins
```

### Arduino Example (LedControl library)

```cpp
#include <LedControl.h>

// DIN, CLK, LOAD, number of MAX7219 devices
LedControl lc = LedControl(11, 13, 10, 1);

void setup() {
  lc.shutdown(0, false);     // wake from power-saving mode
  lc.setIntensity(0, 8);     // brightness 0-15
  lc.clearDisplay(0);
}

void loop() {
  for (int i = 0; i < 8; i++) {
    lc.setDigit(0, i, i, false);
  }
  delay(1000);
}
```

### MicroPython Example (RP2040 / ESP32)

```python
from machine import Pin, SPI
import max7219

spi = SPI(0, baudrate=10000000, sck=Pin(2), mosi=Pin(3))
cs = Pin(5, Pin.OUT)
display = max7219.SevenSegment(spi, cs, num=1)

display.intensity = 8
display.write_number(12345678)
```

## BOM

| Reference | Part | Package | Value / Part No. |
|---|---|---|---|
| U1 | MAX7219CNG | DIP-24 (or SOIC-24) | LED display driver |
| R1 | Resistor | 0603 | 10 kΩ, 1% |
| C1 | Electrolytic | 6.3 mm radial | 10 µF / 16V |
| C2 | Ceramic | 0603 | 100 nF / 16V |
| R2 | Resistor | 0402 | 1 kΩ (LED current limit) |
| LED1 | Green LED | 0603 | Power indicator |
| J1 | Pin header | 2.54 mm, 6-pin | Input / control |
| J2 | Pin header | 2.54 mm, 4-pin | Daisy-chain output |
| J3 | Pin header | 2.54 mm, 12-pin (2x6) | Display connector |

## Common Issues

**Uneven brightness across segments or digits**
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
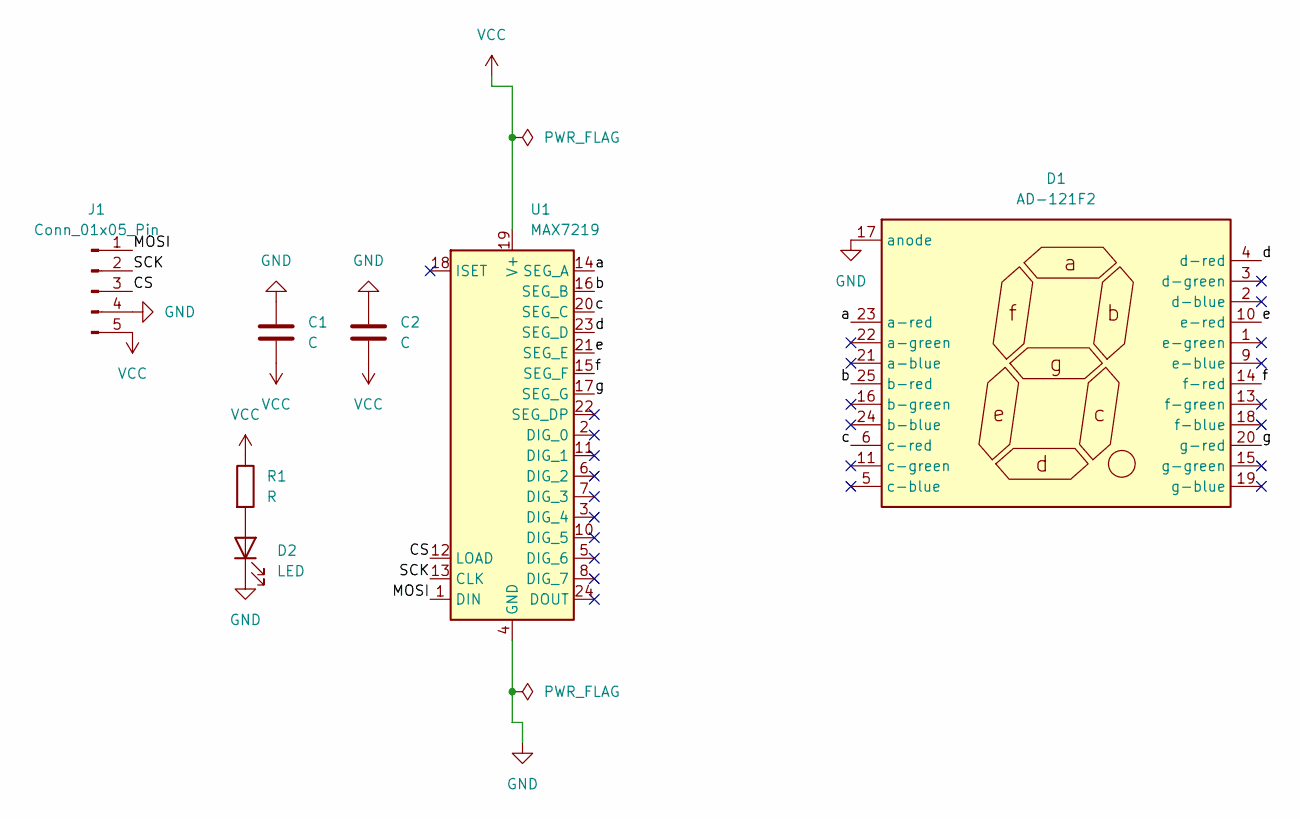
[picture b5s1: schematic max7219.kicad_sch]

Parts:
C1, C2: C; C_0603_1608Metric_Pad1.08x0.95mm_HandSolder
D1: AD-121F2
D2: LED; LED_0805_2012Metric_Pad1.15x1.40mm_HandSolder
J1: Conn_01x05_Pin; PinHeader_1x05_P2.54mm_Vertical
R1: R; R_0603_1608Metric_Pad0.98x0.95mm_HandSolder
U1: MAX7219; DIP-24_W7.62mm

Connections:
/CS: J1.3, U1.12 (LOAD)
/MOSI: J1.1, U1.1 (DIN)
/SCK: J1.2, U1.13 (CLK)
/a: D1.23 (a-red), U1.14 (SEG_A)
/b: D1.25 (b-red), U1.16 (SEG_B)
/c: D1.6 (c-red), U1.20 (SEG_C)
/d: D1.4 (d-red), U1.23 (SEG_D)
/e: D1.10 (e-red), U1.21 (SEG_E)
/f: D1.14 (f-red), U1.15 (SEG_F)
/g: D1.20 (g-red), U1.17 (SEG_G)
GND: C1.1, C2.1, D1.17 (anode), D2.1 (K), J1.4, U1.4 (GND), U1.9 (GND)
unnamed: D2.2 (A), R1.2
VCC: C1.2, C2.2, J1.5, R1.1, U1.19 (V+)

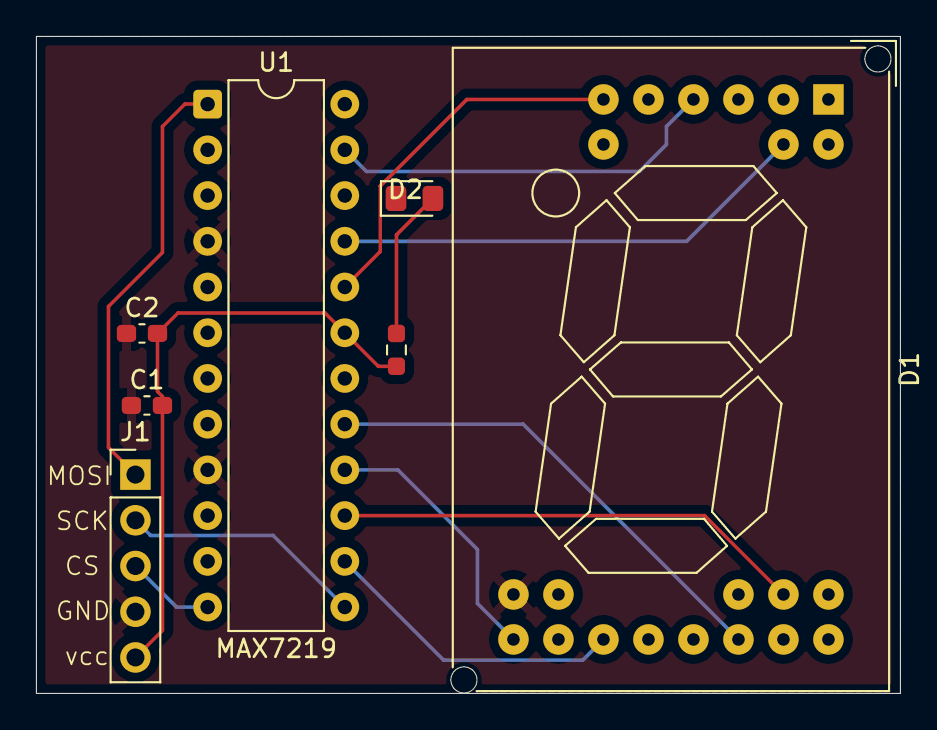
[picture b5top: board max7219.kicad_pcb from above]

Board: 2 copper layers, 48.0 x 36.5 mm, 7 parts (0 on the bottom side), 13 nets.

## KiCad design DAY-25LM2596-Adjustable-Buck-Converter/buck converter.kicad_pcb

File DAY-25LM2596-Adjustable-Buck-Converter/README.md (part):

# LM2596 Adjustable Buck Converter

**Day 25 / 30 — 30-Day PCB Design Challenge**

A general-purpose adjustable step-down (buck) converter board built around the LM2596-ADJ, designed for clean output regulation at switching frequencies up to 150 kHz with a properly compensated feedback network, low-ESR output filtering, and a catch diode sized for the converter's peak switch current — addressing the layout and component-selection mistakes that cause most DIY buck converter boards to be noisy or unstable.

## Overview

The LM2596 is a monolithic step-down switching regulator capable of driving a 3 A load, available in fixed-voltage (3.3 V, 5 V, 12 V) and adjustable (ADJ) variants. The ADJ variant sets output voltage via an external resistor divider feeding the FB pin, referenced to an internal 1.23 V bandgap. Because it is a switching (not linear) regulator, efficiency stays above 70–80% across most of its input range, but this comes at the cost of high di/dt transients at the switch node — a poorly laid-out board will radiate switching noise into the feedback path and cause output ripple or instability regardless of how correct the schematic is.

This board addresses the converter at the level where most hobbyist buck designs go wrong: the catch diode is a Schottky rated for the full 3 A peak switch current with adequate reverse voltage margin, the output inductor is selected for the LM2596's 150 kHz switching frequency rather than reused from an unrelated design, the feedback divider is placed close to the FB pin with the upper resistor routed away from the switch node, and the input/output capacitors are low-ESR types sized for the ripple current the IC datasheet specifies.

## Specifications

| Parameter | Value |
|---|---|
| Input Voltage | 4.5V – 40V DC |
| Output Voltage | 1.23V – 37V (adjustable via potentiometer) |
| Max Output Current | 3A continuous |
| Switching Frequency | 150 kHz (fixed, internal oscillator) |
| Efficiency | Up to 80–88% depending on VIN/VOUT ratio |
| Package | TO-263-5 (D2PAK), surface mount with exposed tab |
| Output Ripple | <50 mV typical with specified LC filter |
| Feedback Reference | 1.23V ±4% |
| PCB | 2-layer, 2 oz copper |

## Why This Layout Matters

Reusing a generic buck converter schematic without attention to the switch-node layout and feedback path is the most common reason these boards perform worse than the IC's datasheet implies:

**Switch node ringing:** The junction between the LM2596 OUT pin, the catch diode cathode, and the inductor carries the full switched current at 150 kHz with fast edges. Trace length here directly adds parasitic inductance, which rings against the diode's junction capacitance and produces voltage spikes that can exceed the diode's reverse rating. This trace is kept as short and wide as the TO-263-5 footprint allows, with the diode placed immediately adjacent to the IC's OUT pin rather than wherever it fit conveniently.

**Feedback path susceptibility:** The FB pin's resistor divider sets the output voltage but also forms a high-impedance node that is sensitive to capacitive coupling from the switch node. Routing the FB trace near or parallel to the switch node trace injects switching noise directly into the regulation loop, which can manifest as output voltage that varies with load or apparent instability even with a correct resistor divider calculation. The feedback trace on this board is routed on the opposite side of the IC from the switch node and kept short.

**Capacitor selection:** The LM2596 datasheet specifies a minimum 680 µF output capacitor with ESR below 0.2 Ω for stable operation across the full load range. A generic electrolytic with higher ESR will pass the "it powers on" test on a bench supply but produce excessive ripple or oscillate under transient load steps. Both input and output capacitors here are selected against the datasheet's ESR and ripple current tables, not just capacitance value.

**Thermal path:** The TO-263-5 package relies on its exposed tab soldered to a copper pour for heat dissipation — there is no heatsink tab to bolt anything to. At 3 A continuous with several volts of dropout, the IC can dissipate over a watt internally, and an undersized copper pour leads to thermal shutdown under sustained load.

## Schematic Overview

**U1 — LM2596-ADJ**
Switching regulator. Pin 1 (VIN) decoupled with bulk and local capacitance. Pin 2 (OUT) connects directly to the catch diode cathode and inductor with minimum trace length. Pin 3 (GND) tied to the ground pour and to the IC's exposed tab pad. Pin 4 (FB) routed to the resistor divider. Pin 5 (ON/OFF) tied to GND (active-low enable, always on).

**D1 — SS34 Schottky Diode**
Catch diode for the switch node. Rated 3 A average, 40 V reverse, with a forward voltage of ~0.5 V at 3 A — significantly lower than a standard silicon diode, which reduces conduction loss and reverse recovery ringing. Placed directly adjacent to the OUT pin.

**L1 — 68 µH Power Inductor**
Selected per the LM2596 datasheet's inductor selection chart for the 150 kHz switching frequency and target output current. Saturation current rated above the 3 A peak switch current with margin. Shielded type used to minimize radiated EMI into the feedback divider and adjacent traces.

**C1 — 220 µF / 50V Electrolytic (Input)**
Bulk input capacitance, low-ESR type, placed as close to the VIN pin as the TO-263-5 footprint allows. Sized against input ripple current rather than just bulk capacitance.

**C2 — 100 nF Ceramic (Input)**
High-frequency input decoupling in parallel with C1, placed within 2 mm of the VIN pin to suppress switching-frequency noise from propagating back into the input supply.

**C3 — 680 µF / 25V Low-ESR Electrolytic (Output)**
Output filter capacitor, meeting the LM2596 datasheet's minimum capacitance and maximum ESR (<0.2 Ω) requirement for loop stability. Undersizing this value or substituting a higher-ESR part is the most common cause of output oscillation in DIY builds of this converter.

**R1 (R_lower) — 1 kΩ, 1%**
Lower leg of the feedback divider, fixed value, from FB to GND.

**RV1 (R_pot) — 10 kΩ Multi-turn Trimmer**
Upper leg of the feedback divider, from VOUT to FB. Output voltage set per:

```
VOUT = 1.23 × (1 + R_pot / R_lower)
```

A multi-turn trimmer is used rather than a single-turn potentiometer for finer adjustment resolution, since a 1% change in R_pot produces a meaningful shift in VOUT near the low end of the adjustment range.

**D2 — Catch diode flyback indicator (optional, not populated by default)**
Footprint provided for an optional Schottky across the inductor for additional flyback protection in high-transient-load applications; left unpopulated for standard use since D1 already provides this function in most operating conditions.

**LED1 — Power indicator**
Green, 0603, with a 1 kΩ series resistor from VOUT. Confirms the regulator is producing output independent of load.

## PCB Design Notes

- Designed in KiCad 8
- 2 oz copper, 2-layer — supports 3 A continuous output current with margin per IPC-2221 trace width tables
- Switch node (U1 OUT → D1 → L1) routed as a single short, wide polygon rather than a thin trace, minimizing parasitic inductance at the highest-dV/dt point in the circuit
- Feedback trace (U1 FB → RV1/R1 junction) routed on the layer and side opposite the switch node, with no parallel routing alongside any switching trace
- Ground pour on both layers, with the LM2596's exposed thermal tab connected to the pour through an array of thermal vias for heat spreading
- Input and output capacitor ground returns connected directly to the IC GND pin region rather than to a distant point on the ground pour, to minimize ground bounce at the IC
- Trimmer (RV1) placed at the board edge for post-assembly accessibility with a screwdriver
- Test points provided on VIN, VOUT, and the switch node for oscilloscope probing
- Mounting holes: 4× M3, 3 mm from board edge at each corner

## Getting Started

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
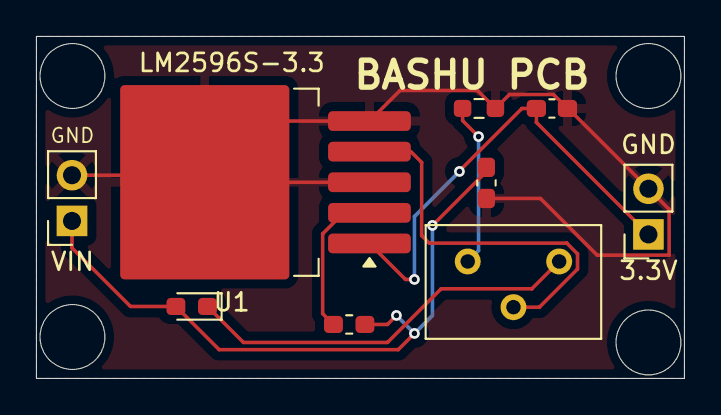
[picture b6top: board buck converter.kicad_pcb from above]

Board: 2 copper layers, 36.0 x 19.0 mm, 9 parts (0 on the bottom side), 7 nets.

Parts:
C: 3.3V; C_0603_1608Metric_Pad1.08x0.95mm_HandSolder
C3: C; C_0603_1608Metric_Pad1.08x0.95mm_HandSolder
D1: D; LED_0603_1608Metric_Pad1.05x0.95mm_HandSolder
J3, J4: Conn_01x02_Pin; PinSocket_1x02_P2.54mm_Vertical
L1: L; L_0603_1608Metric_Pad1.05x0.95mm_HandSolder
R1: R; R_0603_1608Metric_Pad0.98x0.95mm_HandSolder
RV2: R_Potentiometer; Potentiometer_Bourns_3299Y_Vertical
U1: LM2596S-3.3; TO-263-5_TabPin3

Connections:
GND: C.1, C3.2, J3.2, J4.2, R1.2, U1.3 (GND), U1.5 (~ON/OFF)
unnamed: C.2, D1.2 (A), J4.1, L1.2
unnamed: D1.1 (K), RV2.1
unnamed: C3.1, J3.1, U1.1 (VIN)
unnamed: R1.1, RV2.3
unnamed: RV2.2, U1.4 (FB)
unnamed: L1.1, U1.2 (OUT)
